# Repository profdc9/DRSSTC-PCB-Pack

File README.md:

Dual Resonant Solid State Tesla Coil and Solid State Tesla Coil PCB pack.
Copyright (C) 2018 by Daniel L. Marks, licensed under the Created Commons CC-BY-SA 4.0.

These are PCBs for use in DRSSTC/SSTC devices.  They are projects using
the free and open source Kicad software (kicad-pcb.org) version 4.0.7, so these projects
may be modified using this software.  Each file includes the following:

1.  Kicad project, so it can be modified or improved
2.  PDF Schematic
3.  Bill of materials, to refer to when assembling
4.  PNG circuit board picture, to refer to when assembling
5.  Gerber files

The projects, except for the interrupters, are 100 by 100 mm boards with 90 by 90 mm
mounting hole spacing.  These boards may be stacked using M3 spacers. Board of this 
size can often be fabricated for $5 (without shipping) from PCB manufacturers such as
Seeedstudio.  You can save on shipping per board if you have several of
these made at a time, for example, the driver, interrupter, and a bridge board.  

The projects are as follows:

ud27c - a through hole version of the Universal Tesla coil driver, version 2.7C.
          This is based on a design originally by Steve Ward and refined by others including
          Eric Goodchild and Gao Guangyan.  It has substituted the through-hole parts 
          IRF540N/IRF9540N complementary MOSFET pair for the FDD8424H dual MOSFET part.
          It includes phase lead, unlike the Universal Driver v1.3.

ud29 - an experimental version of ud27c that includes skip pulse functionality.  Pulse skip is
          enabled or disabled using a jumper, so it may be used as a normal DRSSTC controller.
		  The board has been built and worked for my coil.
		  
PSoc5-power - a through-hole version of the Universal Driver 3 by Steve Ward and Jens Kerrinnes
          based on the PSoC5 system-on-chip. This includes the functionality for temperature,
		  bus voltage, and bus current sensing.	 This is experimental.  It uses the CYC8KIT-059
		  dev board plugged into the PCB using pin header sockets.

interrupter - a DRSSTC interrupter based on Steve Ward's burst mode interrupter.  It
          includes a place for the IFE97 LED optical fiber transmission unit.  The ability
          to include an external pulse trigger signal has been included for use with audio
          sources.  Also includes a spot on the board for a OneTesla 
		  ATTINY85-based MIDI interrupter which may be flashed with the OneTesla code through
		  the ICSP interface.

lineinterrupter - an experimental interrupter that interrupts on the peak of the AC cycle.
           Interrupting only at the peak of the AC cycle is intended to improve the power factor
		   by minimizing the inrush of current into the bus capacitors as the magnitude of
		   the voltage increases.  
		  
NOTE: You need to flash the included firmware on your ATTINY85 for the MIDI interrupter to work.
Instructions are in the folder "oneTesla-usbInterrupter-software".
		  
half-bridge-sstc - a half-bridge/full-bridge driver designed by myself
          that can either self-oscillate, or take an extetrnal antenna input from a
          Solid State Tesla Coil.  It includes overcurrent and undervoltage protection.
	  
half-bridge-transistor - a layout for a two TO-247 transistor half-bridge that includes
          an area for the capacitor divider network.  Note the polarity on the gates indicated
          on the silkscreening always indicates the negative and positive voltage side of
          the gate; wire the phases of the gates accordingly (oppositely in this case).  This
          convention is followed for all of the layouts.  Space is included for both
          supply bypass/DC Link capacitors and snubber capacitors.
	  
full-bridge-transistor - a layout for a four TO-247 transistor full-bridge.  Space is included
          for supply bypass DC/Link capacitors and snubber capacitors.  The two high-side gates
          should have their polarities wired oppositely, the two low-side gates should
          have their polarities wired oppositely, and the high and low-side gates of each half-bridge
          should be have their polarities wired oppositely.
	  
half-bridge-multi - a layout for an eight TO-247 transistor half-bridge, with four transistors
          of each side of the half-bridge.  The transistors should have a positive temperature
          coefficient to share current more equally.  The high and low-side gates should have their
          polarities wired oppositely.
	  
full-bridge-multi - a layout for an eight TO-247 transistor full-bridge, with two transistors on
          each side of each half bridge.  The two high-side gates should have their 
          polarities wired oppositely, the two low-side gates should have their polarities
          wired oppositely, and the high and low-side gates of each half-bridge
	      should be have their polarities wired oppositely.

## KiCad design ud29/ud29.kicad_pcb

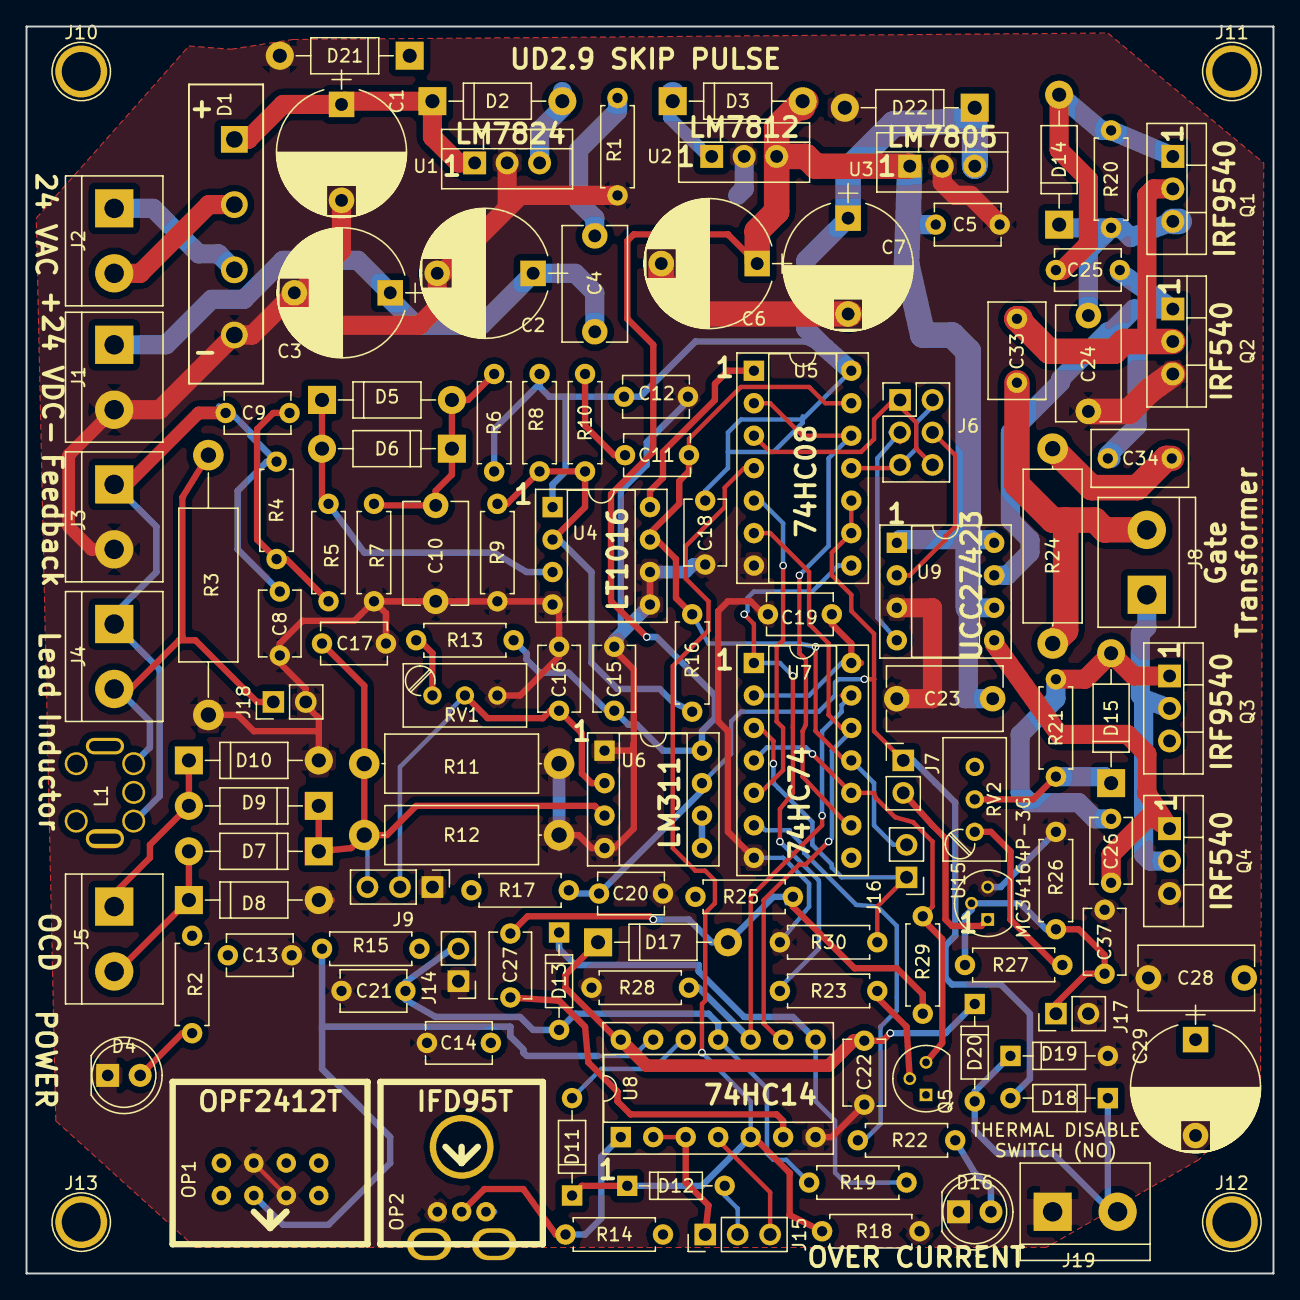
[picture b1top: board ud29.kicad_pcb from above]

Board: 2 copper layers, 97.5 x 97.5 mm, 123 parts (0 on the bottom side), 61 nets.

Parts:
C1, C2, C3, C29: 100 uF; CP_Radial_D10.0mm_P7.50mm
C4, C24, C28: 4.7 uF; C_Disc_D9.0mm_W5.0mm_P7.50mm
C5, C9, C12, C13, C14, C15, C16, C18, C19, C22, C25, C26: 0.1 uF; C_Disc_D5.1mm_W3.2mm_P5.00mm
C6, C7: 330 uF; CP_Radial_D10.0mm_P7.50mm
C8: 150 pF; C_Disc_D5.1mm_W3.2mm_P5.00mm
C10: 1 uF; C_Disc_D8.0mm_W5.0mm_P7.50mm
C11, C17, C20, C21, C27, C37: 1 nF; C_Disc_D5.1mm_W3.2mm_P5.00mm
C23: 1.0 uF; C_Disc_D9.0mm_W5.0mm_P7.50mm
C33: 2.2 uF; C_Disc_D7.5mm_W4.4mm_P5.00mm
C34: 1 uF; C_Disc_D7.5mm_W4.4mm_P5.00mm
D1: D_Bridge_-AA+; Diode_Bridge_18.5x5.5_4321
D2, D3, D21: 1N4007; D_DO-41_SOD81_P10.16mm_Horizontal
D4, D16: LED; LED_D5.0mm
D5, D6, D7, D8, D9, D10: 1N5818; D_DO-41_SOD81_P10.16mm_Horizontal
D11, D12, D13, D18, D19, D20: 1N4148; D_DO-35_SOD27_P7.62mm_Horizontal
D14, D15, D17: 1N4148; D_DO-41_SOD81_P10.16mm_Horizontal
D22: 1N4733A; D_DO-41_SOD81_P10.16mm_Horizontal
J1, J2, J3, J4, J5, J8, J19: Conn_01x02; TerminalBlock_bornier-2_P5.08mm
J6: Conn_02x03_Odd_Even; Pin_Header_Straight_2x03_Pitch2.54mm
J7, J14, J16, J17, J18: Conn_01x02; Pin_Header_Straight_1x02_Pitch2.54mm
J9, J15: Conn_01x03; Pin_Header_Straight_1x03_Pitch2.54mm
J10, J11, J12, J13: Conn_01x01; 1pin
L1: SLOT7; CoilCraft_Slot_7
OP1: OPF2412T
OP2: IFD95
Q1, Q3: IRF9540N; TO-220-3_Vertical
Q2, Q4: IRF540N; TO-220-3_Vertical
Q5: 2N3906; TO-92_Molded_Narrow
R1: 1R; R_Axial_DIN0207_L6.3mm_D2.5mm_P7.62mm_Horizontal
R2, R7, R9, R10, R22, R26: 470R; R_Axial_DIN0207_L6.3mm_D2.5mm_P7.62mm_Horizontal
R3: 51R; R_Axial_DIN0414_L11.9mm_D4.5mm_P20.32mm_Horizontal
R4, R16, R19: 100k; R_Axial_DIN0207_L6.3mm_D2.5mm_P7.62mm_Horizontal
R5, R6, R8, R14, R15, R17, R18, R20, R21, R27, R28: 1k; R_Axial_DIN0207_L6.3mm_D2.5mm_P7.62mm_Horizontal
R11, R12: 5.1R; R_Axial_DIN0414_L11.9mm_D4.5mm_P15.24mm_Horizontal
R13, R25: 1.8k; R_Axial_DIN0207_L6.3mm_D2.5mm_P7.62mm_Horizontal
R23, R29, R30: 10k; R_Axial_DIN0207_L6.3mm_D2.5mm_P7.62mm_Horizontal
R24: 15R; R_Axial_DIN0414_L11.9mm_D4.5mm_P15.24mm_Horizontal
RV1: 10k; Potentiometer_Trimmer_Bourns_3296W
RV2: 5k; Potentiometer_Trimmer_Bourns_3296W
U1: LM7824_TO220; TO-220-3_Vertical
U2: LM7812_TO220; TO-220-3_Vertical
U3: LM7805_TO220; TO-220-3_Vertical
U4: TL3116; DIP-8_W7.62mm_Socket
U5: 74HC08; DIP-14_W7.62mm_Socket
U6: LM311; DIP-8_W7.62mm_Socket
U7: 74HC74; DIP-14_W7.62mm_Socket
U8: 74HC14; DIP-14_W7.62mm_Socket
U9: UCC27243; DIP-8_W7.62mm_Socket
U15: MC34164; TO-92_Molded_Narrow

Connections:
+5V: C7.1, C12.1, C13.1, C14.1, C18.1, C19.1, C22.2, D17.1, D20.1, D22.1, OP1.2, OP2.3, Q5.1, R2.1, R6.1, R8.1, R14.2, R15.1, R17.2, R25.2, U3.3, U4.1, U5.14, U7.2, U7.14, U8.14
+12V: C5.1, C6.1, C15.2, C23.2, D3.2, R13.1, U2.3, U3.1, U6.8, U9.1, U9.6, U9.8
+24V: C2.1, C3.1, C4.1, C24.1, C28.1, C29.1, D2.2, D3.1, D14.1, D15.1, D21.1, J1.1, Q1.3, Q3.3, R20.1, R21.1, RV2.2, U1.3, U2.1
GND: C1.2, C2.2, C3.2, C5.2, C6.2, C7.2, C8.2, C10.1, C12.2, C13.2, C14.2, C15.1, C16.1, C17.2, C18.2, C19.2, C20.1, C21.1, C22.1, C23.1, C24.2, C28.2, C29.2, C37.1, D1.1, D4.1, D8.2, D10.2, D16.1, D19.2, D21.2, D22.2, J1.2, J3.2, J9.1, J14.1, J17.2, J18.2, J19.1, OP1.3, OP1.7, OP2.1, Q2.3, Q4.3, R1.2, R3.2, R7.2, R9.2, R11.2, R12.2, R18.1, R26.2, R28.2, R30.1, RV1.3, U1.2, U2.2, U3.2, U4.4, U4.5, U4.6, U5.7, U6.1, U6.4, U7.7, U8.7, U9.3, U15.3
INTERRUPTER: D11.1, D12.1, R18.2, U5.4, U8.5
INTERRUPTEREDGE: Q5.3, R29.1, U7.4, U7.10
unnamed: C1.1, D1.4, D2.1, U1.1
unnamed: C4.2, R1.1
unnamed: C8.1, C9.2, J3.1, J4.1, L1.3, R4.2
unnamed: C9.1, R4.1, R5.2
unnamed: C10.2, D5.2, D6.1, R6.2, R7.1
unnamed: C11.1, J16.2, R16.2, U4.7, U5.13, U7.11
unnamed: C11.2, R10.2
unnamed: C16.2, J9.2, RV1.2, U6.2
unnamed: C17.1, D7.1, D9.1, J9.3, R11.1, R12.1, U6.3
unnamed: C21.2, D13.2, J14.2, R19.1, U8.11
unnamed: C25.1, D14.2, Q1.1, R20.2
unnamed: C25.2, Q2.1, U9.7
unnamed: C26.1, D15.2, Q3.1, R21.2
unnamed: C26.2, Q4.1, U9.5
unnamed: C27.1, U8.6
unnamed: C33.1, C34.1, Q1.2, Q2.2
unnamed: C33.2, J8.2, R24.2
unnamed: C34.2, R24.1
unnamed: C37.2, J17.1, R26.1, R27.2, U15.2
unnamed: D1.2, J2.1
unnamed: D1.3, J2.2
unnamed: D4.2, R2.2
unnamed: D5.1, D6.2, R5.1, U4.3
unnamed: D7.2, D8.1, J5.2
unnamed: D9.2, D10.1, J5.1
unnamed: D11.2, U8.12
unnamed: D12.2, J15.2
unnamed: D13.1, R19.2, U8.8
unnamed: D16.2, R22.2
unnamed: D18.1, D19.1, D20.2, J19.2
unnamed: J6.1, J6.6, U5.3
unnamed: J6.2, J6.5, U5.11
unnamed: J6.3, U9.4
unnamed: J6.4, U9.2
unnamed: J7.2, U15.1
unnamed: J8.1, Q3.2, Q4.2
unnamed: J15.1, U8.2, U8.3
unnamed: J15.3, U8.4
unnamed: J16.1, R30.2, U7.3
unnamed: J4.2, J18.1, L1.1, R3.1
unnamed: OP1.6, R15.2, U8.13
unnamed: OP2.2, R14.1, U8.1
unnamed: Q5.2, R23.2
unnamed: R8.2, R9.1, R10.1, R16.1, U4.2
unnamed: R13.2, RV1.1
unnamed: R22.1, U7.6
unnamed: R23.1, U5.8, U7.1
unnamed: R27.1, RV2.1
unnamed: R28.1, U7.13, U8.10
unnamed: U4.8, U5.1
unnamed: U5.5, U7.5
unnamed: U5.6, U7.12, U8.9
unnamed: U5.2, U5.12, U7.9
unnamed: U6.5, U6.6
UNDERVOLT: C20.2, D18.2, J7.1, R17.1, U5.9, U5.10, U6.7

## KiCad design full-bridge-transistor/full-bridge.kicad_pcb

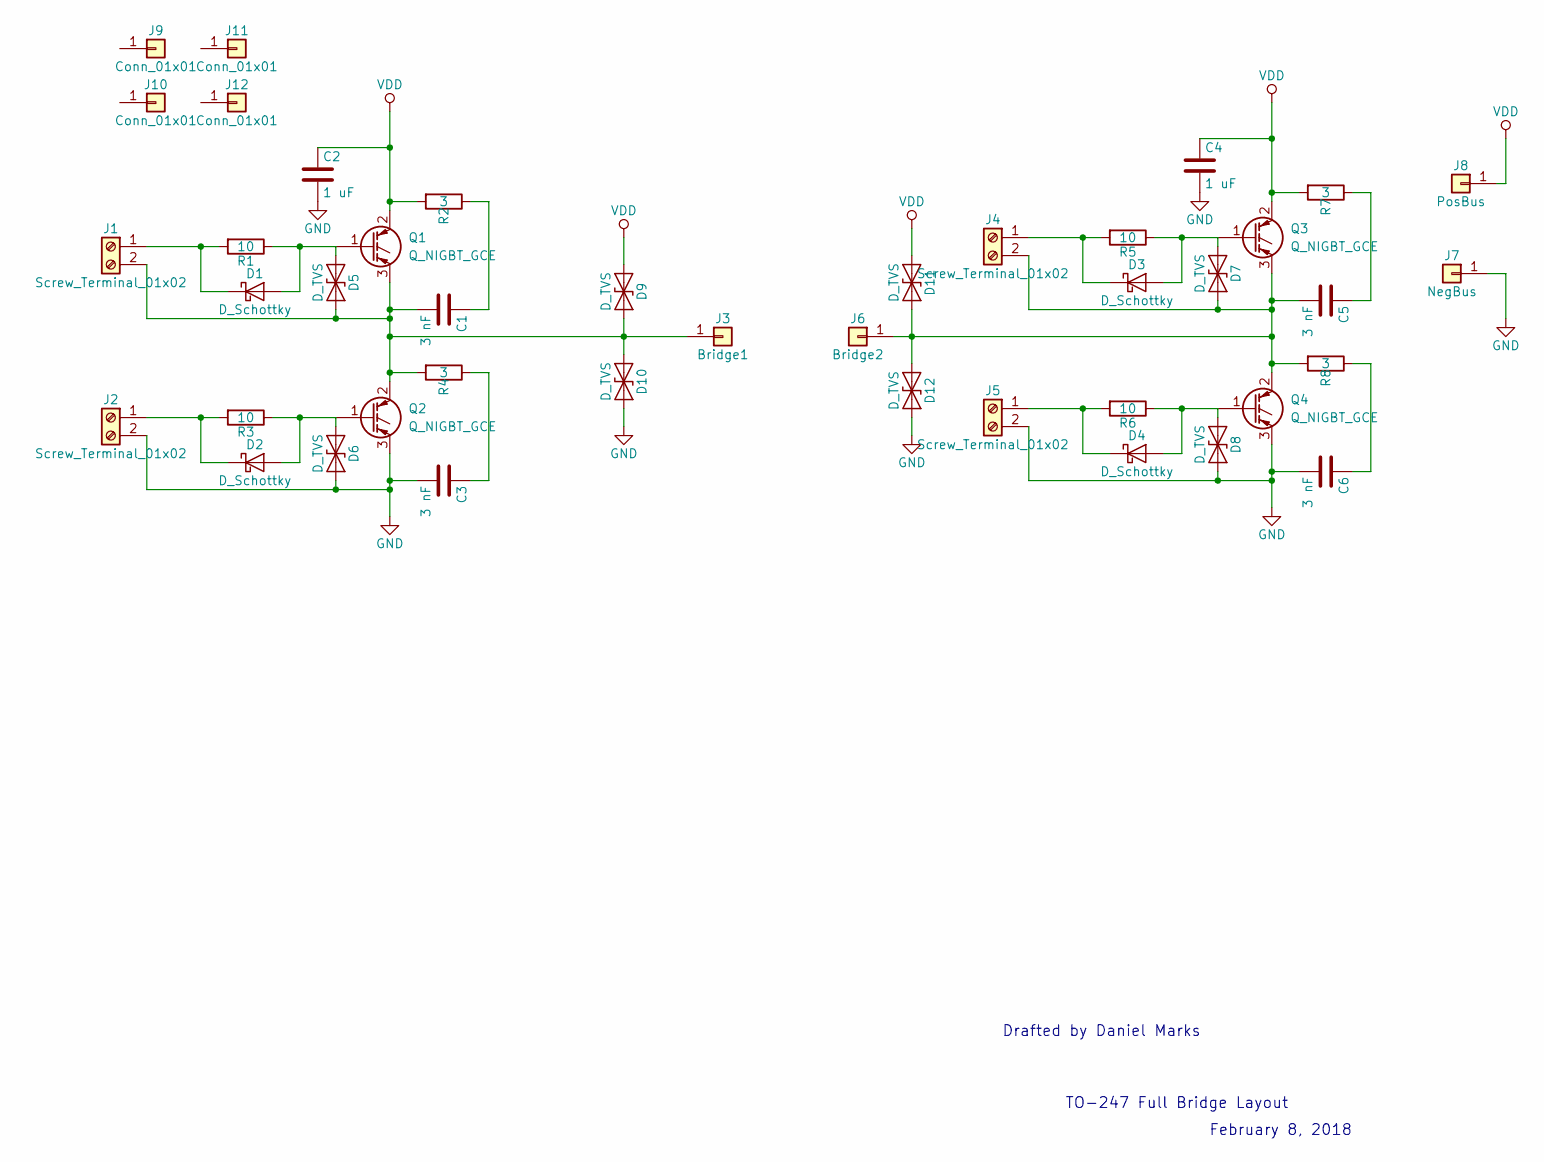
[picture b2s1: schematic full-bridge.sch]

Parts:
C1, C3, C5, C6: 3 nF; C_Rect_L11.5mm_W6.9mm_P10.00mm_MKT
C2, C4: 1 uF; C_Rect_L24.0mm_W12.2mm_P22.50mm_MKT
D1, D2, D3, D4: D_Schottky; D_DO-41_SOD81_P10.16mm_Horizontal
D5, D6, D7, D8: D_TVS; D_DO-41_SOD81_P10.16mm_Horizontal
D9, D10, D11, D12: D_TVS; D_DO-201_P12.70mm_Horizontal
J1, J2, J4, J5: Screw_Terminal_01x02; TerminalBlock_bornier-2_P5.08mm
J3: Bridge1; 1pin
J6: Bridge2; 1pin
J7: NegBus; 1pin
J8: PosBus; 1pin
J9, J10, J11, J12: Conn_01x01; 1pin
Q1, Q2, Q3, Q4: Q_NIGBT_GCE; TO-247_TO-3P_Vertical
R1, R3, R5, R6: 10; R_Axial_DIN0411_L9.9mm_D3.6mm_P12.70mm_Horizontal
R2, R4, R7, R8: 3; R_Axial_DIN0414_L11.9mm_D4.5mm_P15.24mm_Horizontal

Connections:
GND: C2.2, C3.2, C4.2, C6.2, D6.2 (A2), D8.2 (A2), D10.2 (A2), D12.2 (A2), J2.2, J5.2, J7.1, Q2.3 (E), Q4.3 (E)
unnamed: C1.1, R2.1
unnamed: C1.2, D5.2 (A2), D9.2 (A2), D10.1 (A1), J1.2, J3.1, Q1.3 (E), Q2.2 (C), R4.2
unnamed: C3.1, R4.1
unnamed: C5.1, R7.1
unnamed: C5.2, D7.2 (A2), D11.2 (A2), D12.1 (A1), J4.2, J6.1, Q3.3 (E), Q4.2 (C), R8.2
unnamed: C6.1, R8.1
unnamed: D1.1 (K), J1.1, R1.2
unnamed: D1.2 (A), D5.1 (A1), Q1.1 (G), R1.1
unnamed: D2.1 (K), J2.1, R3.2
unnamed: D2.2 (A), D6.1 (A1), Q2.1 (G), R3.1
unnamed: D3.1 (K), J4.1, R5.2
unnamed: D3.2 (A), D7.1 (A1), Q3.1 (G), R5.1
unnamed: D4.1 (K), J5.1, R6.2
unnamed: D4.2 (A), D8.1 (A1), Q4.1 (G), R6.1
VDD: C2.1, C4.1, D9.1 (A1), D11.1 (A1), J8.1, Q1.2 (C), Q3.2 (C), R2.2, R7.2

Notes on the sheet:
TO-247 Full Bridge Layout
Drafted by Daniel Marks
February 8, 2018

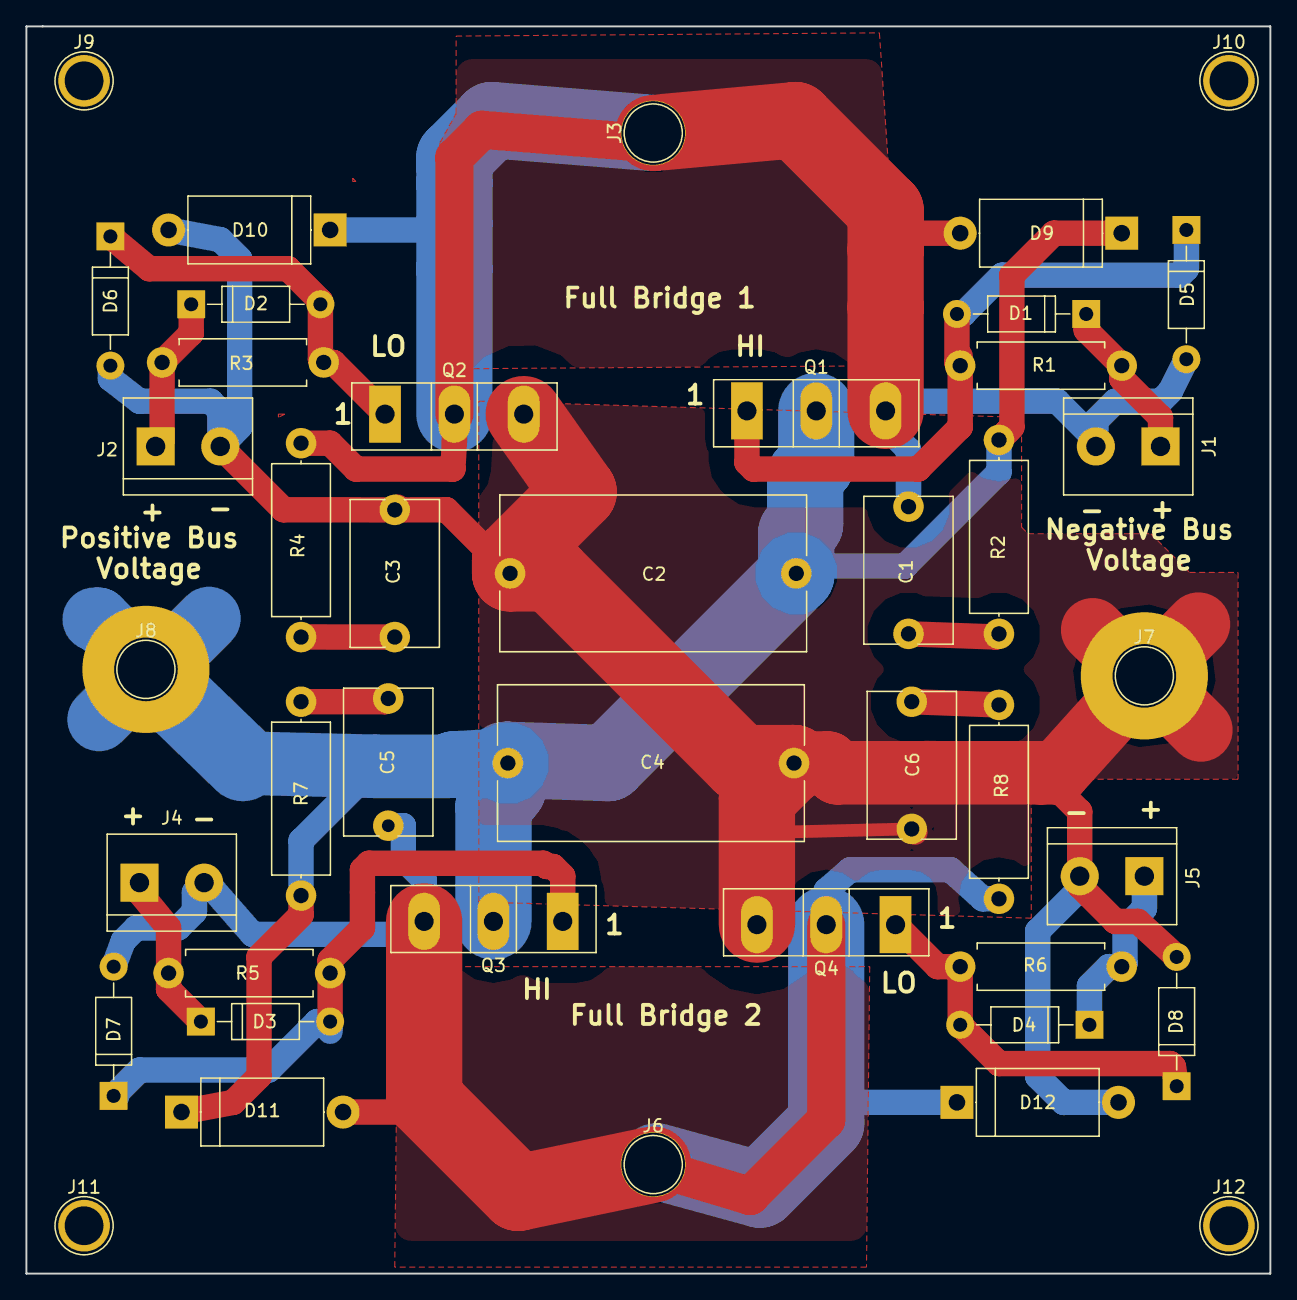
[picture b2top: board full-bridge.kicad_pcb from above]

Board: 2 copper layers, 97.8 x 98.0 mm, 42 parts (0 on the bottom side), 16 nets.

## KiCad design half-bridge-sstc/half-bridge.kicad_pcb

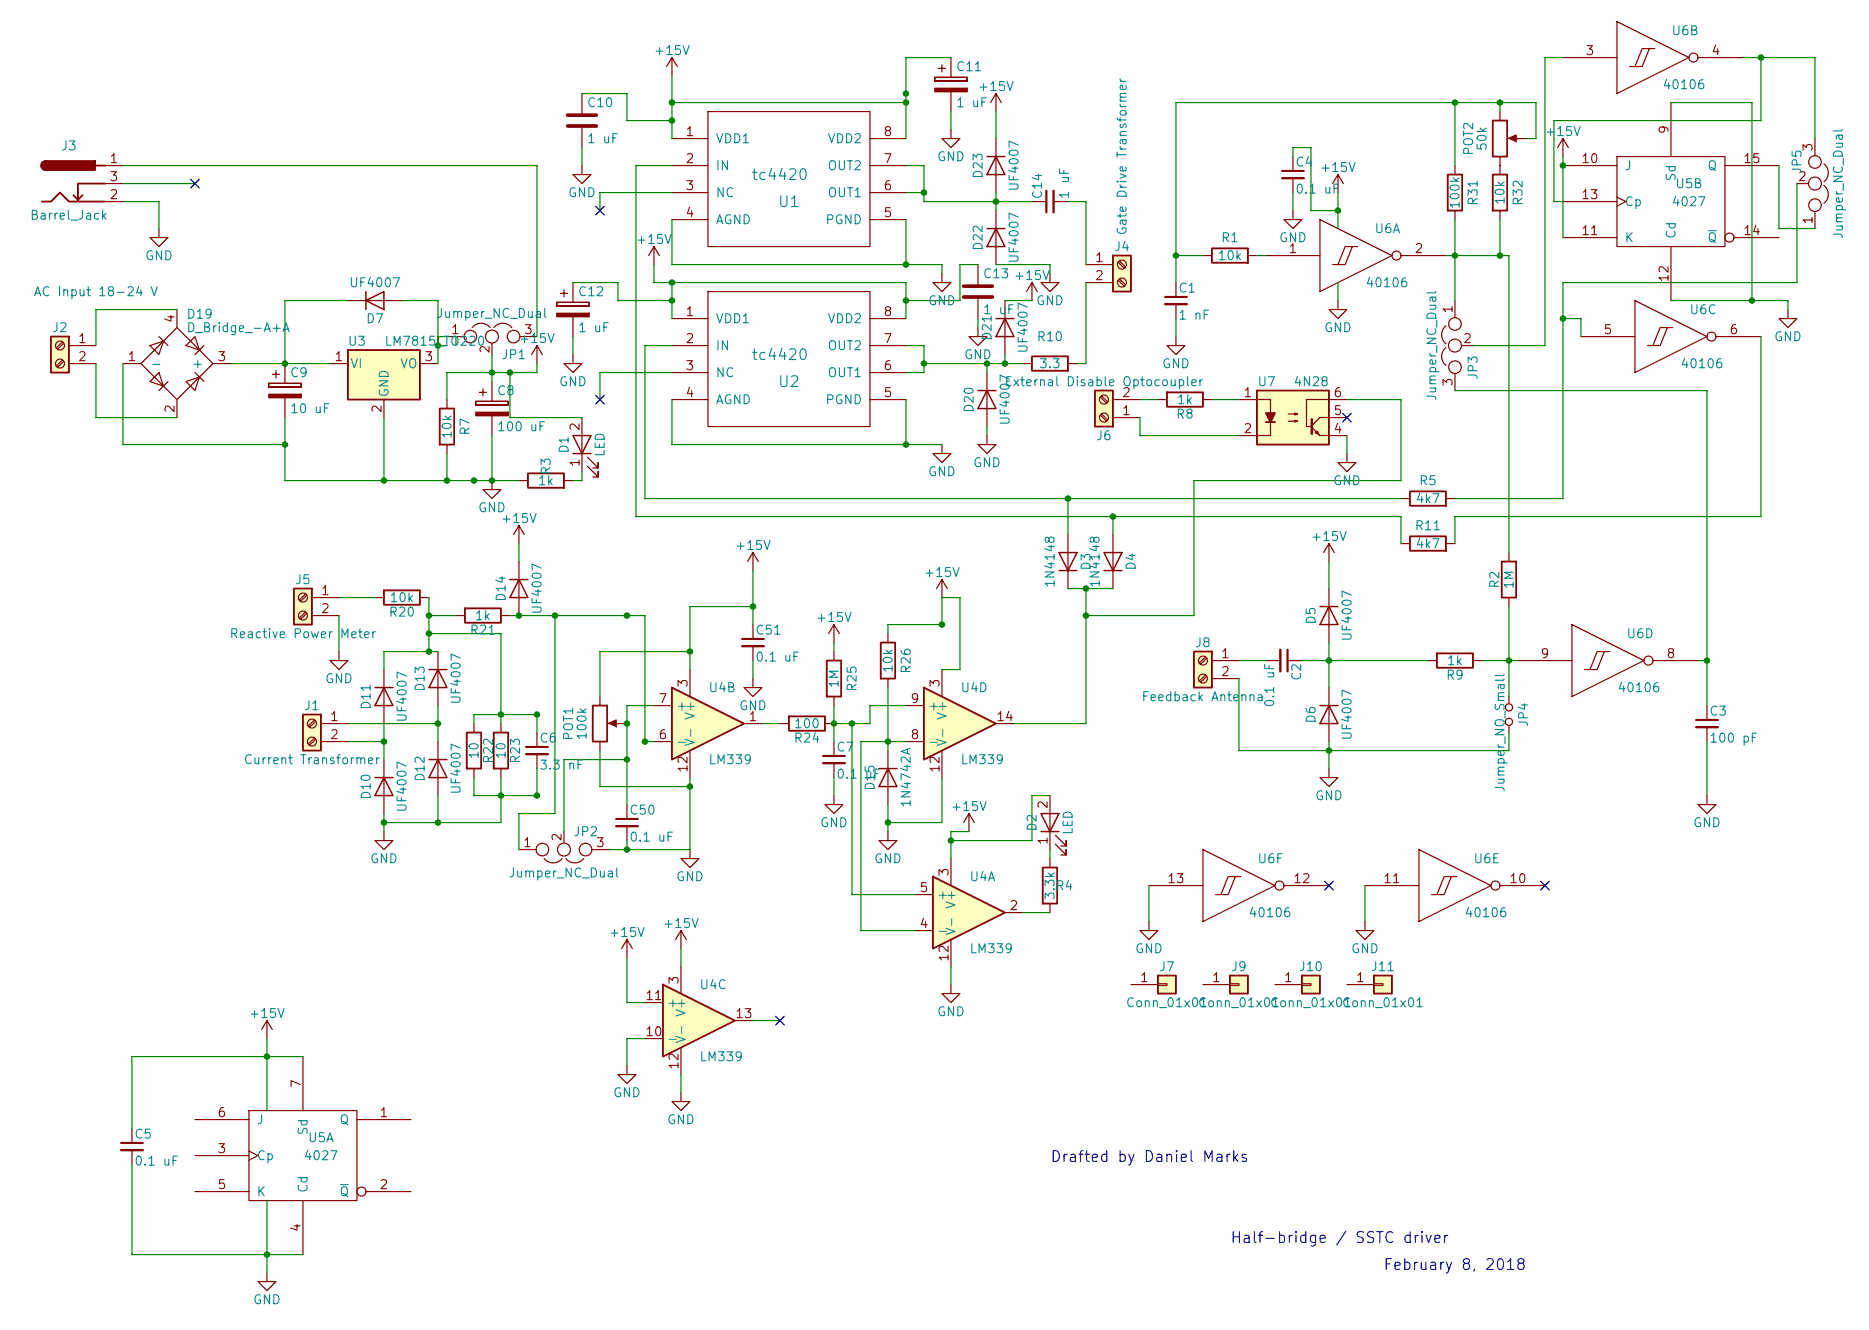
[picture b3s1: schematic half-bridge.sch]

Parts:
C1: 1 nF; C_Disc_D7.5mm_W4.4mm_P5.00mm
C2, C4, C5, C7, C50, C51: 0.1 uF; C_Disc_D7.5mm_W4.4mm_P5.00mm
C3: 100 pF; C_Disc_D7.5mm_W4.4mm_P5.00mm
C6: 3.3 nF; C_Disc_D7.5mm_W5.0mm_P7.50mm
C8: 100 uF; CP_Radial_D14.0mm_P7.50mm
C9: 10 uF; CP_Radial_D8.0mm_P5.00mm
C10, C13: 1 uF; C_Disc_D7.5mm_W5.0mm_P7.50mm
C11, C12: 1 uF; CP_Radial_D8.0mm_P5.00mm
C14: 1 uF; C_Disc_D9.0mm_W5.0mm_P7.50mm
D1, D2: LED; LED_D5.0mm
D3, D4: 1N4148; D_DO-41_SOD81_P7.62mm_Horizontal
D5, D6, D7, D10, D11, D12, D13, D14, D20, D21, D22, D23: UF4007; D_DO-41_SOD81_P7.62mm_Horizontal
D15: 1N4742A; D_DO-41_SOD81_P7.62mm_Horizontal
D19: D_Bridge_-A+A; Diode_Bridge_18.5x5.5
J1: Current Transformer; TerminalBlock_Phoenix_MKDS1.5-2pol
J2: AC Input 18-24 V; TerminalBlock_Phoenix_MKDS1.5-2pol
J3: Barrel_Jack; BARREL_JACK
J4: Gate Drive Transformer; TerminalBlock_Phoenix_MKDS1.5-2pol
J5: Reactive Power Meter; TerminalBlock_Phoenix_MKDS1.5-2pol
J6: External Disable Optocoupler; TerminalBlock_Phoenix_MKDS1.5-2pol
J7, J9, J10, J11: Conn_01x01; 1pin
J8: Feedback Antenna; TerminalBlock_Phoenix_MKDS1.5-2pol
JP1, JP2, JP3, JP5: Jumper_NC_Dual; Pin_Header_Straight_1x03_Pitch2.54mm
JP4: Jumper_NO_Small; Pin_Header_Straight_1x02_Pitch2.54mm
POT1: 100k; Potentiometer_WirePads
POT2: 50k; Potentiometer_WirePads
R1, R7, R20, R26, R32: 10k; R_Axial_DIN0207_L6.3mm_D2.5mm_P10.16mm_Horizontal
R2, R25: 1M; R_Axial_DIN0207_L6.3mm_D2.5mm_P10.16mm_Horizontal
R3, R8, R9, R21: 1k; R_Axial_DIN0207_L6.3mm_D2.5mm_P10.16mm_Horizontal
R4: 3.3k; R_Axial_DIN0207_L6.3mm_D2.5mm_P10.16mm_Horizontal
R5, R11: 4k7; R_Axial_DIN0207_L6.3mm_D2.5mm_P10.16mm_Horizontal
R10: 3.3; R_Axial_DIN0414_L11.9mm_D4.5mm_P15.24mm_Horizontal
R22, R23: 10; R_Axial_DIN0414_L11.9mm_D4.5mm_P15.24mm_Horizontal
R24: 100; R_Axial_DIN0207_L6.3mm_D2.5mm_P10.16mm_Horizontal
R31: 100k; R_Axial_DIN0207_L6.3mm_D2.5mm_P10.16mm_Horizontal
U1, U2: tc4420; DIP-8_W7.62mm_Socket
U3: LM7815_TO220; TO-220_Vertical
U4: LM339; DIP-14_W7.62mm_Socket
U5: 4027; DIP-16_W7.62mm_Socket
U6: 40106; DIP-14_W7.62mm_Socket
U7: 4N28; DIP-6_W7.62mm_Socket

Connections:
+15V: C4.1, C5.1, C8.1, C10.1, C11.1, C12.1, C13.1, C51.1, D1.2 (A), D2.2 (A), D5.1 (K), D14.1 (K), D21.1 (K), D23.1 (K), JP1.2, POT1.1, R7.1, R25.1, R26.1, U1.1 (VDD1), U1.8 (VDD2), U2.1 (VDD1), U2.8 (VDD2), U4.3 (V+), U4.11 (+), U5.7 (Sd), U5.10 (J), U5.11 (K), U5.16 (VDD), U6.14 (VDD)
GND: C1.2, C3.2, C4.2, C5.2, C6.2, C7.2, C8.2, C9.2, C10.2, C11.2, C12.2, C13.2, C50.2, C51.2, D6.2 (A), D10.2 (A), D12.2 (A), D15.2 (A), D19.1 (-), D20.2 (A), D22.2 (A), J3.2, J5.2, J8.2, JP2.3, JP4.2, POT1.3, R3.1, R7.2, R22.2, R23.2, U1.4 (AGND), U1.5 (PGND), U2.4 (AGND), U2.5 (PGND), U3.2 (GND), U4.10 (-), U4.12 (V-), U5.4 (Cd), U5.8 (VSS), U5.9 (Sd), U5.12 (Cd), U6.7 (VSS), U6.11 (In), U6.13 (In), U7.4
unnamed: C1.1, POT2.1, POT2.2, R1.1, R31.1
unnamed: C2.1, D5.2 (A), D6.1 (K), R9.2
unnamed: C2.2, J8.1
unnamed: C3.1, JP3.3, U6.8 (Out)
unnamed: C6.1, D11.1 (K), D13.1 (K), R20.1, R21.2, R22.1, R23.1
unnamed: C7.1, R24.1, R25.2, U4.5 (+), U4.9 (+)
unnamed: C9.1, D7.1 (K), D19.3 (+), U3.1 (VI)
unnamed: C14.1, D22.1 (K), D23.2 (A), U1.6 (OUT1), U1.7 (OUT2)
unnamed: C14.2, J4.1
unnamed: C50.1, JP2.2, POT1.2, U4.7 (+)
unnamed: D1.1 (K), R3.2
unnamed: D2.1 (K), R4.1
unnamed: D3.1 (K), D4.1 (K), U4.14, U7.6
unnamed: D3.2 (A), R5.1, U2.2 (IN)
unnamed: D4.2 (A), R11.1, U1.2 (IN)
unnamed: D7.2 (A), JP1.1, U3.3 (VO)
unnamed: D10.1 (K), D11.2 (A), J1.2
unnamed: D12.1 (K), D13.2 (A), J1.1
unnamed: D14.2 (A), JP2.1, R21.1, U4.6 (-)
unnamed: D15.1 (K), R26.2, U4.4 (-), U4.8 (-)
unnamed: D19.2, J2.2
unnamed: D19.4, J2.1
unnamed: D20.1 (K), D21.2 (A), R10.1, U2.6 (OUT1), U2.7 (OUT2)
unnamed: J3.1, JP1.3
unnamed: J4.2, R10.2
unnamed: J5.1, R20.2
unnamed: J6.1, U7.2
unnamed: J6.2, R8.2
unnamed: JP3.1, R2.2, R31.2, R32.2, U6.2 (Out)
unnamed: JP3.2, U6.3 (In)
unnamed: JP4.1, R2.1, R9.1, U6.9 (In)
unnamed: JP5.1, U5.15 (Q)
unnamed: JP5.2, R5.2, U6.5 (In)
unnamed: JP5.3, U5.13 (Cp), U6.4 (Out)
unnamed: POT2.3, R32.1
unnamed: R1.2, U6.1 (In)
unnamed: R4.2, U4.2
unnamed: R8.1, U7.1
unnamed: R11.2, U6.6 (Out)
unnamed: R24.2, U4.1

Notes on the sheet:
Half-bridge / SSTC driver
Drafted by Daniel Marks
February 8, 2018

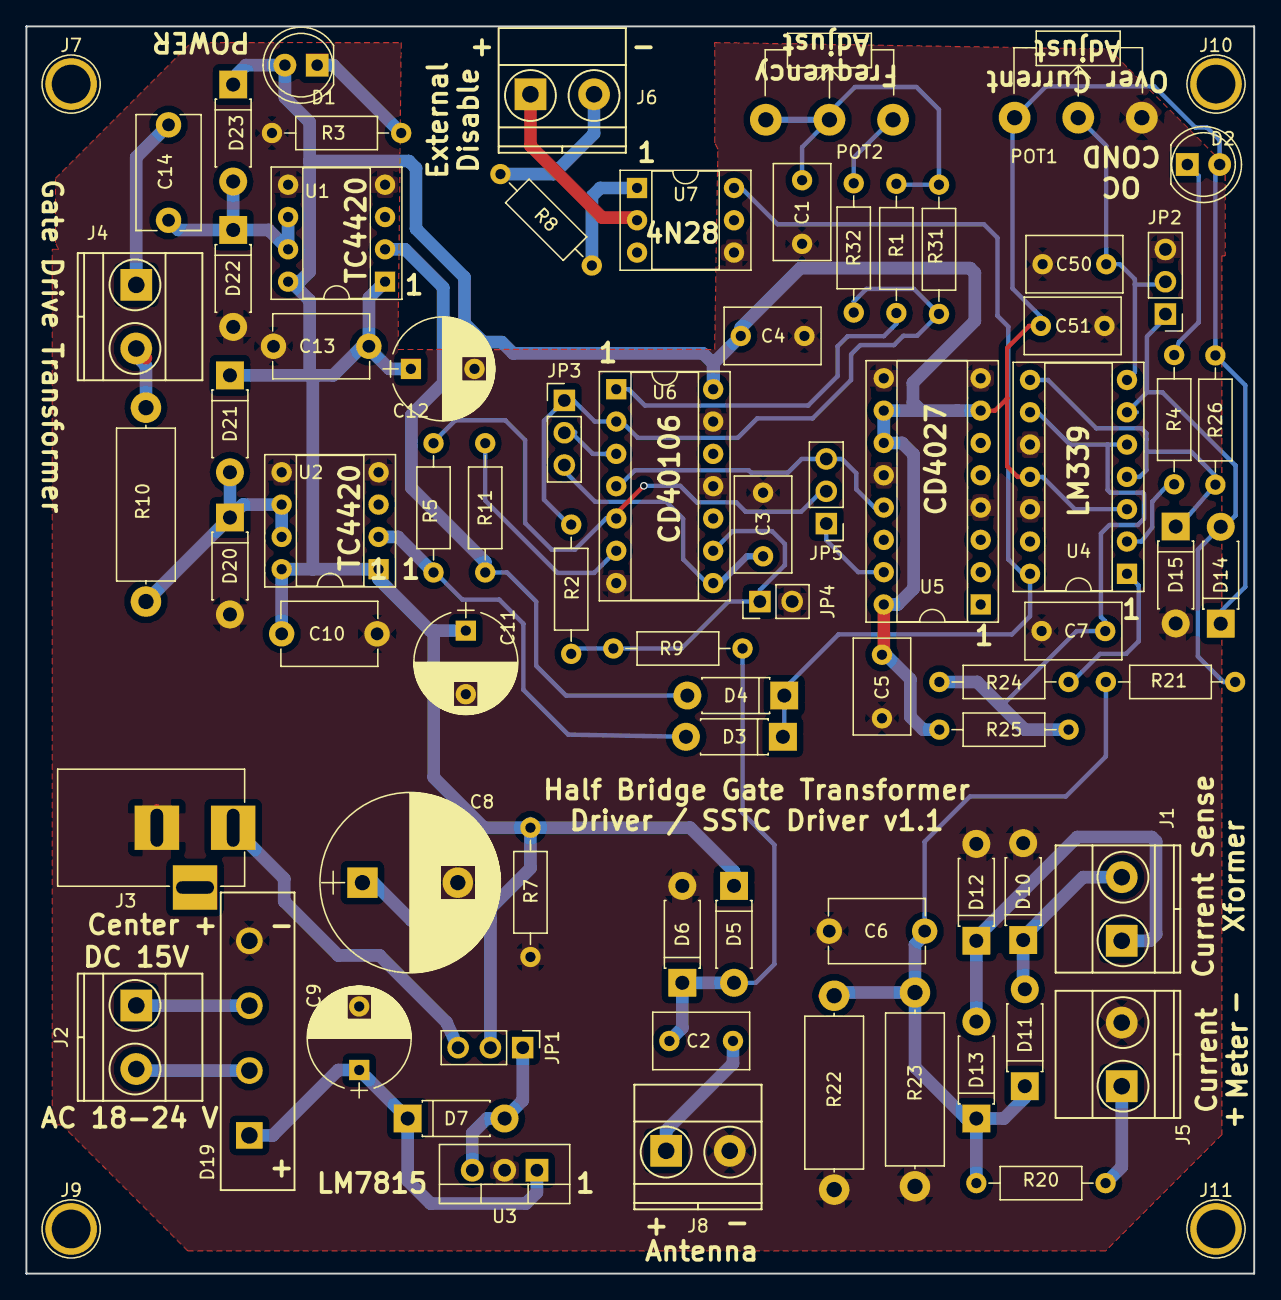
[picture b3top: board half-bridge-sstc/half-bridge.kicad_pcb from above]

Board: 2 copper layers, 96.5 x 98.0 mm, 78 parts (0 on the bottom side), 42 nets.

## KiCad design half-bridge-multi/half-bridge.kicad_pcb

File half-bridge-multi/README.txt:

For this board to work properly, jumper wires must be soldered across the board with
a wire insulated to at least 600 volts:

1.  Between the two points labeled Bridge1
2.  Between the two points labeled Bridge2
3.  Between the two points labeled Bridge3
4.  Between the two points labeled Bridge4
These provide lower inductance paths between the two sides of the bridge to prevent
spikes on the bus during switching transitions.

An optional extra snubber capacitor may be soldered at the Cap+ and Cap-
connections where the PosBus and NegBus connections are made.

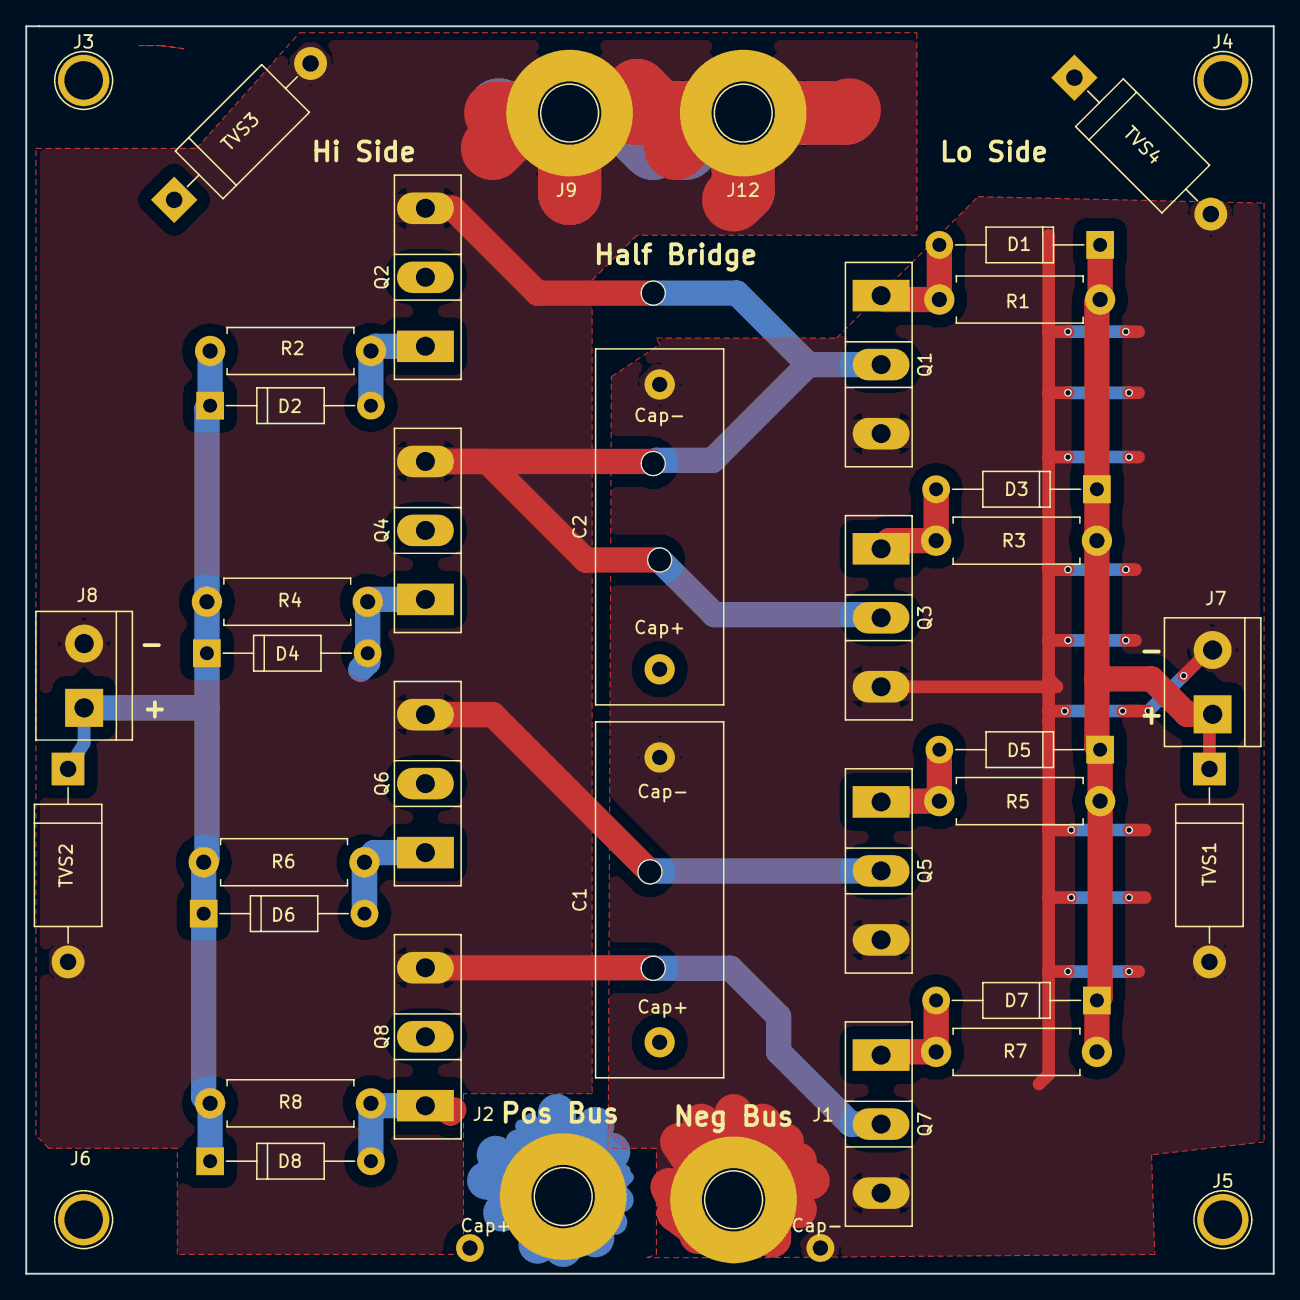
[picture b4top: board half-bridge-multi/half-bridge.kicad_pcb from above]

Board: 2 copper layers, 98.6 x 98.6 mm, 42 parts (0 on the bottom side), 13 nets.

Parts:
C1, C2: 1 uF; C_Rect_L28.0mm_W10.0mm_P22.50mm_MKS4
D1, D2, D3, D4, D5, D6, D7, D8: D_Schottky; D_DO-41_SOD81_P12.70mm_Horizontal
J1: NegBus; 1pin
J2: PosBus; 1pin
J3, J4, J5, J6: Conn_01x01; 1pin
J7, J8: Screw_Terminal_01x02; TerminalBlock_bornier-2_P5.08mm
J9, J12: Bridge1; 1pin
J27, J28: Conn_01x01; smallpin
Q1, Q2, Q3, Q4, Q5, Q6, Q7, Q8: Q_NIGBT_GCE; TO-247_TO-3P_Vertical
R1, R2, R3, R4, R5, R6, R7, R8: 10; R_Axial_DIN0411_L9.9mm_D3.6mm_P12.70mm_Horizontal
TVS1, TVS2, TVS3, TVS4: D; D_DO-201_P15.24mm_Horizontal

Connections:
GND: C1.2, C2.2, J1.1, J7.2, J28.1, Q1.3, Q3.3, Q5.3, Q7.3, TVS1.2, TVS4.2
unnamed: D1.1, D3.1, D5.1, D7.1, J7.1, R1.2, R3.2, R5.2, R7.2, TVS1.1
unnamed: D1.2, Q1.1, R1.1
unnamed: D2.1, D4.1, D6.1, D8.1, J8.1, R2.2, R4.2, R6.2, R8.2, TVS2.1
unnamed: D2.2, Q2.1, R2.1
unnamed: D3.2, Q3.1, R3.1
unnamed: D4.2, Q4.1, R4.1
unnamed: D5.2, Q5.1, R5.1
unnamed: D6.2, Q6.1, R6.1
unnamed: D7.2, Q7.1, R7.1
unnamed: D8.2, Q8.1, R8.1
unnamed: J8.2, J9.1, J12.1, Q1.2, Q2.3, Q3.2, Q4.3, Q5.2, Q6.3, Q7.2, Q8.3, TVS2.2, TVS3.2, TVS4.1
VDD: C1.1, C2.1, J2.1, J27.1, Q2.2, Q4.2, Q6.2, Q8.2, TVS3.1
